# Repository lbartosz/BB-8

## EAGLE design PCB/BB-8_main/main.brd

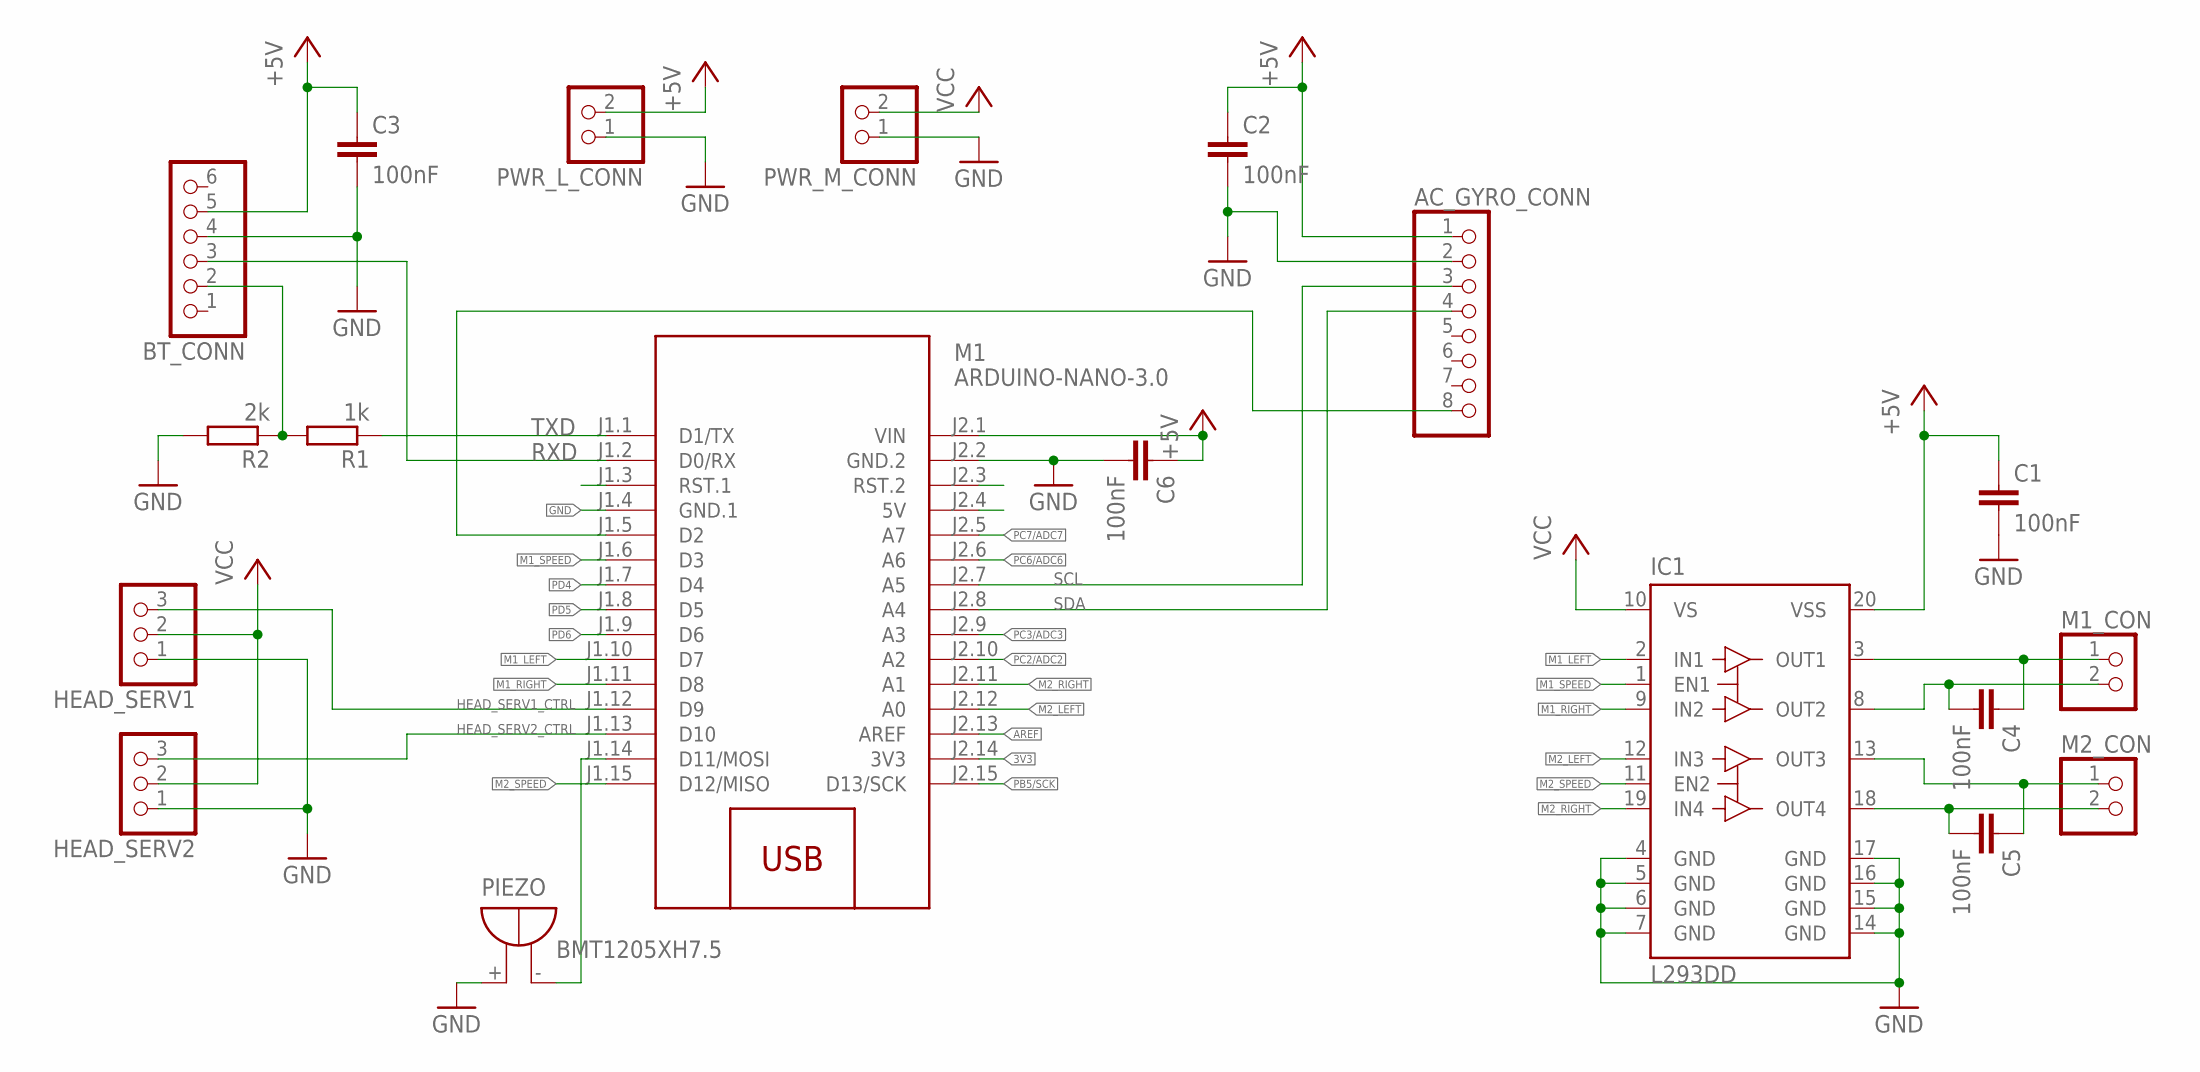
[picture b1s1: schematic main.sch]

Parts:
AC_GYRO_CONN: PINHD-1X8; 1X08
BT_CONN: PINHD-1X6; 1X06
C1, C2, C3, C4, C5, C6: 100nF; C0805
HEAD_SERV1, HEAD_SERV2: PINHD-1X3; 1X03
IC1: L293DD; SO20
M1: ARDUINO-NANO-3.0
M1_CON, M2_CON: PINHD-1X2; 1X02
PIEZO: BMT1205XH7.5
PWR_L_CONN: PINHD-1X2; 1X02
PWR_M_CONN: PINHD-1X2; 1X02
R1: 1k; 0207/10
R2: 2k; 0207/10

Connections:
3V3: M1.J2.14 (3V3)
+5V: AC_GYRO_CONN.1, BT_CONN.5, C1.1, C2.1, C3.1, C6.1, IC1.20 (VSS), M1.J2.1 (VIN), PWR_L_CONN.2
AC_GYRO_INT: AC_GYRO_CONN.8, M1.J1.5 (D2)
AREF: M1.J2.13 (AREF)
GND: AC_GYRO_CONN.2, BT_CONN.4, C1.2, C2.2, C3.2, C6.2, HEAD_SERV1.1, HEAD_SERV2.1, IC1.4 (GND), IC1.5 (GND), IC1.6 (GND), IC1.7 (GND), IC1.14 (GND), IC1.15 (GND), IC1.16 (GND), IC1.17 (GND), M1.J1.4 (GND.1), M1.J2.2 (GND.2), PIEZO.+, PWR_L_CONN.1, PWR_M_CONN.1, R2.2
HEAD_SERV1_CTRL: HEAD_SERV1.3, M1.J1.12 (D9)
HEAD_SERV2_CTRL: HEAD_SERV2.3, M1.J1.13 (D10)
M1_LEFT: IC1.2 (IN1), M1.J1.10 (D7)
M1_RIGHT: IC1.9 (IN2), M1.J1.11 (D8)
M1_SPEED: IC1.1 (EN1), M1.J1.6 (D3)
M2_LEFT: IC1.12 (IN3), M1.J2.12 (A0)
M2_RIGHT: IC1.19 (IN4), M1.J2.11 (A1)
M2_SPEED: IC1.11 (EN2), M1.J1.15 (D12/MISO)
unnamed: C4.1, IC1.3 (OUT1), M1_CON.1
unnamed: C4.2, IC1.8 (OUT2), M1_CON.2
unnamed: C5.2, IC1.18 (OUT4), M2_CON.2
unnamed: C5.1, IC1.13 (OUT3), M2_CON.1
unnamed: BT_CONN.2, R1.2, R2.1
PB4: M1.J1.14 (D11/MOSI), PIEZO.-
PB5/SCK: M1.J2.15 (D13/SCK)
PC2/ADC2: M1.J2.10 (A2)
PC3/ADC3: M1.J2.9 (A3)
PC6/ADC6: M1.J2.6 (A6)
PC7/ADC7: M1.J2.5 (A7)
PD4: M1.J1.7 (D4)
PD5: M1.J1.8 (D5)
PD6: M1.J1.9 (D6)
RXD: BT_CONN.3, M1.J1.2 (D0/RX)
SCL: AC_GYRO_CONN.3, M1.J2.7 (A5)
SDA: AC_GYRO_CONN.4, M1.J2.8 (A4)
TXD: M1.J1.1 (D1/TX), R1.1
VCC: HEAD_SERV1.2, HEAD_SERV2.2, IC1.10 (VS), PWR_M_CONN.2

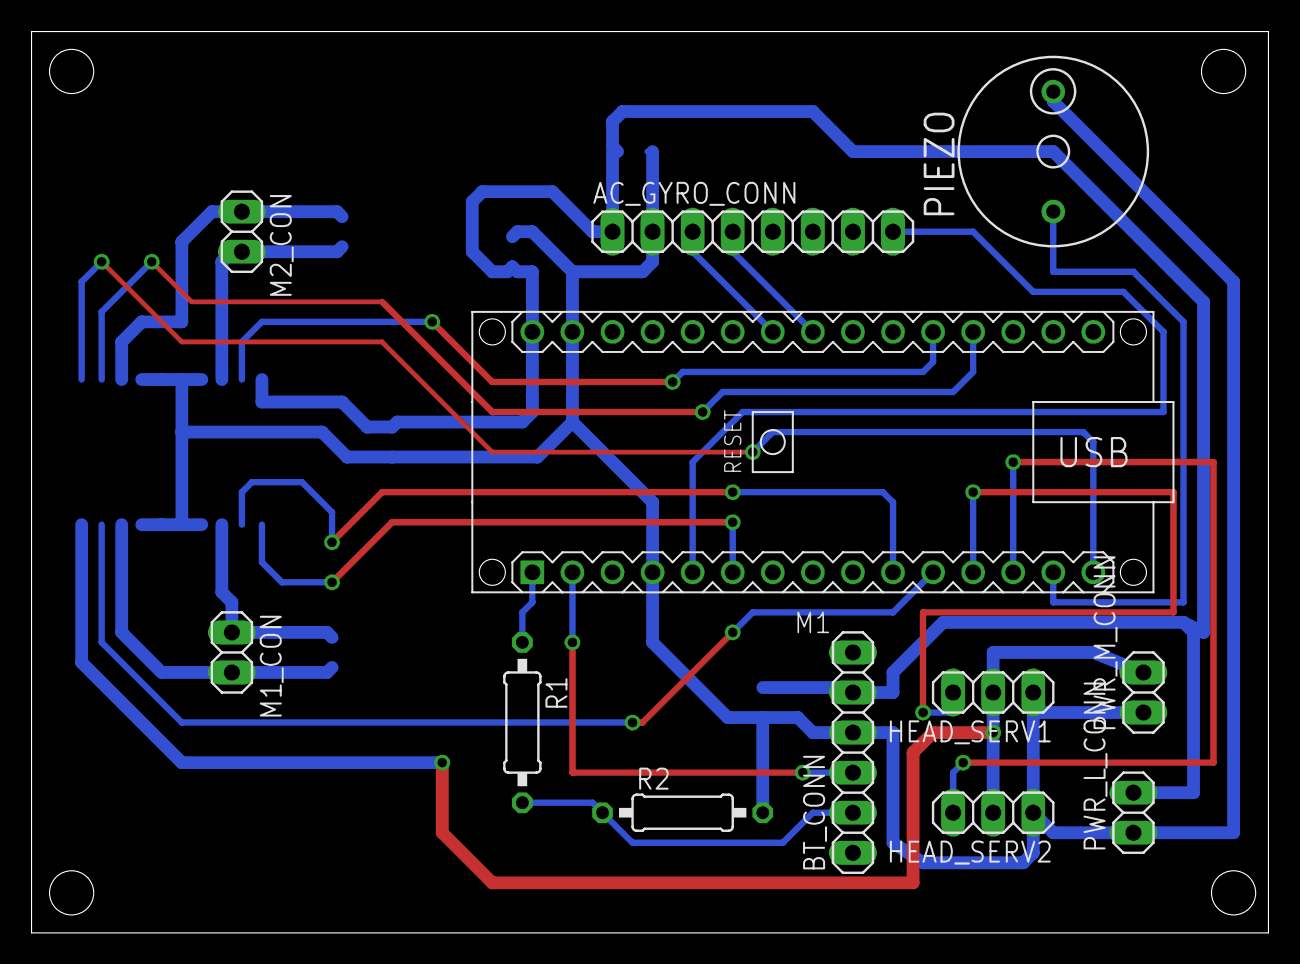
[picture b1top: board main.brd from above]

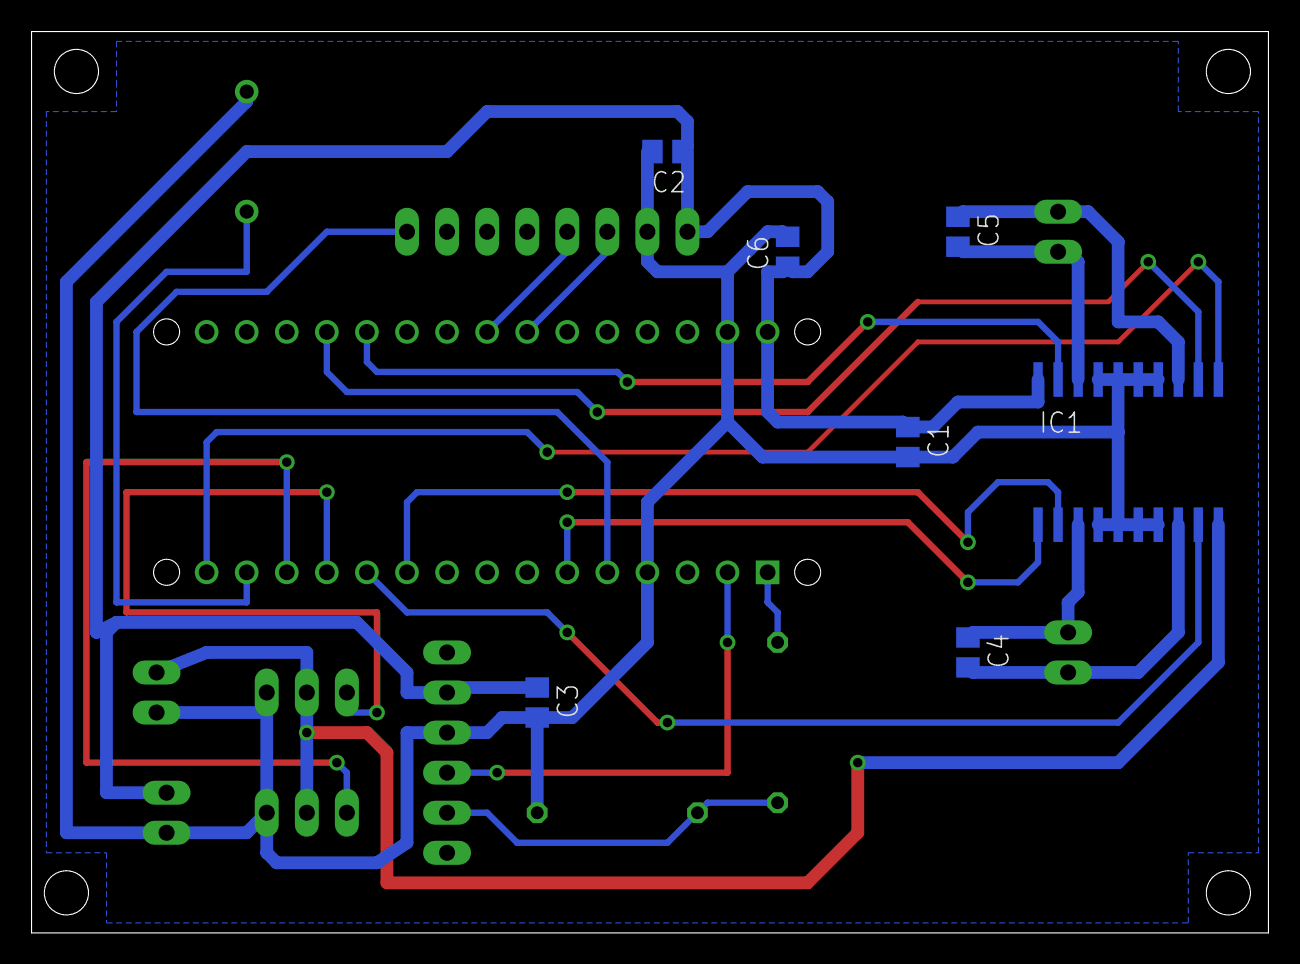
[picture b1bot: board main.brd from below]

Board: 2 copper layers, 78.4 x 57.1 mm, 19 parts (7 on the bottom side), 22 nets.

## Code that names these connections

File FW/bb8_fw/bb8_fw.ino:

/*
 Name:    bb8_fw.ino
 Created:  1/15/2016 8:01:30 PM
 Author:  Lukasz Bartosz
*/

#include <Servo.h>
#include <SoftwareSerial.h>

//==================================
// enable/disable test mode here
#define TEST_ENABLED 0

//==================================
// enable debug uart logging
#define DEBUG

//==================================
// define debug macros
#ifdef DEBUG
  #define DEBUG_PRINT(x) Serial.print(x)
  #define DEBUG_PRINTDEC(x) Serial.print(x, DEC)
  #define DEBUG_PRINTLN(x) Serial.println(x)
  #define DEBUG_MSG_INTERVAL 500
  unsigned long last_debug_msg = 0;
#else
  #define DEBUG_PRINT(x)
  #define DEBUG_PRINTDEC(x)
  #define DEBUG_PRINTLN(x)
#endif // DEBUG


// =================================
// pin assignments here and other constants
#define SERVO_MIN 1000
#define SERVO_MAX 2400

#define PIN_HEAD_SERVO_X 9  // D9 PB1 OC1A
#define PIN_HEAD_SERVO_Y 10  // D10 PB2 OC1B

#define PIN_M1_SPEED 3    // D3 PD3
#define PIN_M1_LEFT 7    // D7 PD7
#define PIN_M1_RIGHT 8    // D8 PB0 

#define PIN_M2_SPEED 6  // D6 PD6
#define PIN_M2_LEFT 14    // PC0 ADC0
#define PIN_M2_RIGHT 15    // PC1 ADC1

#define PIN_PIEZO 11    // D12 PB3 MOSI

#define PIN_BTSERIAL_RX 16
#define PIN_BTSERIAL_TX 17

#define MIN_MOTOR_SPEED 80
#define MAX_MOTOR_SPEED 81
#define MAX_TRANSLATION 1 //this has to be MAX_MOTOR_SPEED minus MIN_MOTOR_SPEED
#define MAX_ROTATION 5    //this is max value that can be added/substracted from translation when turning
#define ROT_STEP 1    // this will be added to rotation once turn control is pressed
#define CTRL_RELEASE_DELAY 200
 
#define LEFT 'L'
#define RIGHT 'R'
#define FORWARD 'F'
#define BACKWARD 'B'
#define STOP 'S'
#define SOUND 'P'
#define NOOP 'N'


// globals
Servo servo_head_x;
Servo servo_head_y;

SoftwareSerial bt_serial(PIN_BTSERIAL_RX, PIN_BTSERIAL_TX);

int translation = 0;
int rotation = 0;
int m1_speed = 0;
int m2_speed = 0;

char last_ctrls_received = NOOP;
unsigned long last_ctrl_time = 0;


//==================================
// functions declarations
void test_actuators(void);
void update_actuators(int, int);
int set_m1_speed(int = MAX_MOTOR_SPEED);
int set_m2_speed(int = MAX_MOTOR_SPEED);
void full_stop(bool = true, bool = true);
void make_sound(void);

//==================================
// SYSTEM SETUP
void setup() {
  // head control servos
  servo_head_x.attach(PIN_HEAD_SERVO_X, SERVO_MIN, SERVO_MAX);
  servo_head_y.attach(PIN_HEAD_SERVO_Y, SERVO_MIN, SERVO_MAX);
  
  pinMode(PIN_M1_LEFT, OUTPUT);
  pinMode(PIN_M1_RIGHT, OUTPUT);
  pinMode(PIN_M2_LEFT, OUTPUT);
  pinMode(PIN_M2_RIGHT, OUTPUT);
  
  pinMode(PIN_PIEZO, OUTPUT);
  
  Serial.begin(115200);
  bt_serial.begin(115200);

#ifdef DEBUG
  last_debug_msg = millis();
#endif // DEBUG


}

//==================================
// MAIN LOOP
void loop() {
  // --------------------------------------
  // test code to check actuators
  while(TEST_ENABLED) {
    test_actuators();
  }

  // receive ctrl via bt
  if (bt_serial.available()) {
    last_ctrl_time = millis();
    last_ctrls_received = bt_serial.read();
  } else {
    if (millis() - last_ctrl_time > CTRL_RELEASE_DELAY) {
      last_ctrl_time = millis();
      last_ctrls_received = NOOP;
    }
  }
  
  // some ifs here to read what to do from ctrl command
  switch (last_ctrls_received)  {
  case SOUND:
    last_ctrls_received = NOOP;
    make_sound();
    break;
  case FORWARD:
    rotation = 0;
    if (translation < 0) {
      full_stop();
      translation = 0;
    } else {
      translation = MAX_TRANSLATION;
    }
    break;
  case BACKWARD:
    rotation = 0;
    if (translation > 0) {
      full_stop();
      translation = 0;
    } else {
      translation = -MAX_TRANSLATION;
    }
    break;
  case LEFT:
    translation = 0;
    if (rotation <= 0) {
      rotation = -MAX_ROTATION;
    } else {
      rotation = 0;
    }
    break;
  case RIGHT:
    translation = 0;
    if (rotation >= 0) {
      rotation = MAX_ROTATION;
    } else {
      rotation = 0;
    }
    break;
  case STOP:
    last_ctrls_received = NOOP;
    translation = 0;
    rotation = 0;
    full_stop();
    break;
  case NOOP:
    translation = 0;
    rotation = 0;
    full_stop();
    break;
  default:
    break;
  }


#ifdef DEBUG
  if (millis() - last_debug_msg > DEBUG_MSG_INTERVAL) {
    last_debug_msg = millis();
    DEBUG_PRINT(" |BT_COMM: ");  DEBUG_PRINT(last_ctrls_received);
    DEBUG_PRINT(" |T: "); DEBUG_PRINT(translation);
    DEBUG_PRINT(" |R: "); DEBUG_PRINT(rotation);
    DEBUG_PRINT(" |M1: "); DEBUG_PRINT(m1_speed);
    DEBUG_PRINT(" |M2: "); DEBUG_PRINTLN(m2_speed);
  }
#endif // DEBUG

  // update actuators
  update_actuators(translation, rotation);


}

//==================================
// function definitions

void test_actuators(void) {
  make_sound();
}

void update_actuators(int translation, int rotation) {
  int m1_target_speed = 0;
  int m2_target_speed = 0;

  if (translation > 0) {
    m1_target_speed = MIN_MOTOR_SPEED + translation;
    m2_target_speed = MIN_MOTOR_SPEED + translation;
  }
  else if (translation < 0) {
    m1_target_speed = translation - MIN_MOTOR_SPEED;
    m2_target_speed = translation - MIN_MOTOR_SPEED;
  }

  if (abs(rotation) > 0) {
    m1_target_speed = max(MIN_MOTOR_SPEED, m1_target_speed) + rotation;
    m2_target_speed = max(MIN_MOTOR_SPEED, m1_target_speed) - rotation;
  }
  
  m1_speed = set_m1_speed(m1_target_speed);
  m2_speed = set_m2_speed(m2_target_speed);
}

int set_m1_speed(int target_speed) {
  // set motor speed to given in argument
  // return current engine speed

  if (target_speed > 0) {
    if (m1_speed >= 0) {
      digitalWrite(PIN_M1_LEFT, HIGH);
      digitalWrite(PIN_M1_RIGHT, LOW);
    }
    else {
      full_stop(true, false);
      return(0);
    }
  }
  else if (target_speed < 0) {
    if (m1_speed <= 0) {
      digitalWrite(PIN_M1_LEFT, LOW);
      digitalWrite(PIN_M1_RIGHT, HIGH);
    }
    else {
      full_stop(true, false);
      return(0);
    }
  }
  else {
    full_stop(true, false);
    return(0);
  }

  analogWrite(PIN_M1_SPEED, abs(target_speed));
  return (target_speed);
}

int set_m2_speed(int target_speed) {
  // set motor speed to given in argument
  // return current engine speed

  if (target_speed > 0) {
    if (m2_speed >= 0) {
      digitalWrite(PIN_M2_LEFT, HIGH);
      digitalWrite(PIN_M2_RIGHT, LOW);
    }
    else {
      full_stop(false, true);
      return(0);
    }
  }
  else if (target_speed < 0) {
    if (m2_speed <= 0) {
      digitalWrite(PIN_M2_LEFT, LOW);
      digitalWrite(PIN_M2_RIGHT, HIGH);
    }
    else {
      full_stop(false, true);
      return(0);
    }
  }
  else {
    digitalWrite(PIN_M2_LEFT, LOW);
    digitalWrite(PIN_M2_RIGHT, LOW);
    analogWrite(PIN_M2_SPEED, 255);
    return(0);
  }

  analogWrite(PIN_M2_SPEED, abs(target_speed));
  return (target_speed);
}


void full_stop(bool stop_m1, bool stop_m2) {
  if (stop_m1) {
    digitalWrite(PIN_M1_LEFT, LOW);
    digitalWrite(PIN_M1_RIGHT, LOW);
    analogWrite(PIN_M1_SPEED, 0);
    m1_speed = 0;
  }
  if (stop_m2) {
    digitalWrite(PIN_M2_LEFT, LOW);
    digitalWrite(PIN_M2_RIGHT, LOW);
    analogWrite(PIN_M2_SPEED, 0);
    m2_speed = 0;
  }
}

void make_sound(void) {
  for (int i = 200; i >= 0; i--) {
    digitalWrite(PIN_PIEZO, LOW);
    delayMicroseconds(1000);
    digitalWrite(PIN_PIEZO, HIGH);
    delayMicroseconds(1000);
  }
  digitalWrite(PIN_PIEZO, LOW);
}

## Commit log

2016-01-17 Adding BB-8 first PCB and FW files
2016-01-17 Adding basic motor control functions
2016-01-18 Basic tidy up
2016-01-18 Updating PCB layout - almost done, perform check
2016-01-19 Adding GND polygon
2016-01-19 final version for print
2016-01-31 Added first code to test communication between Android app and HC-05
2016-02-17 adding proper main structure. Beep on button press now works
2016-02-22 Translating forward and backward to translation changes
2016-02-22 rest
2016-02-24 Changes to translation and motor speed functions
2016-02-25 Forward and backward motor updates
2016-02-25 Rotation updates based on keypress
2016-02-28 Adding rotation control
2016-03-02 Fix for M2 not working (pin reassignment)
2016-03-06 Implementing inertion for BB-8 move - not finished!
2016-03-13 pushing innertion work from laptop
2016-03-16 Another changes for inertion - does not work correctly yet
2016-04-13 Fixes in adjusting translation when pressing F/B
2016-04-14 train fixes
2016-06-08 2nd approach first changes
2016-06-09 Simplifying parsing control command. No speed adjustment, just simple 0 or max speed. Resetting ctrl command and stopping if no ctrl commands supplied not yet in.
2016-06-27 Changes in handling bt commands
2016-06-27 Fixed backward direction with speed fixed at 90. Rotation still needs to be done.
2016-11-26 Some latest changes to sync to laptop
2016-12-29 Switching BT serial to software controlled pins. This is version that has correct behavior when releasing control button on the phone

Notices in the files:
parts and their libraries:
diy-modules: Released under the Creative Commons Attribution 4.0 International License: http://creativecommons.org/licenses/by/4.0
